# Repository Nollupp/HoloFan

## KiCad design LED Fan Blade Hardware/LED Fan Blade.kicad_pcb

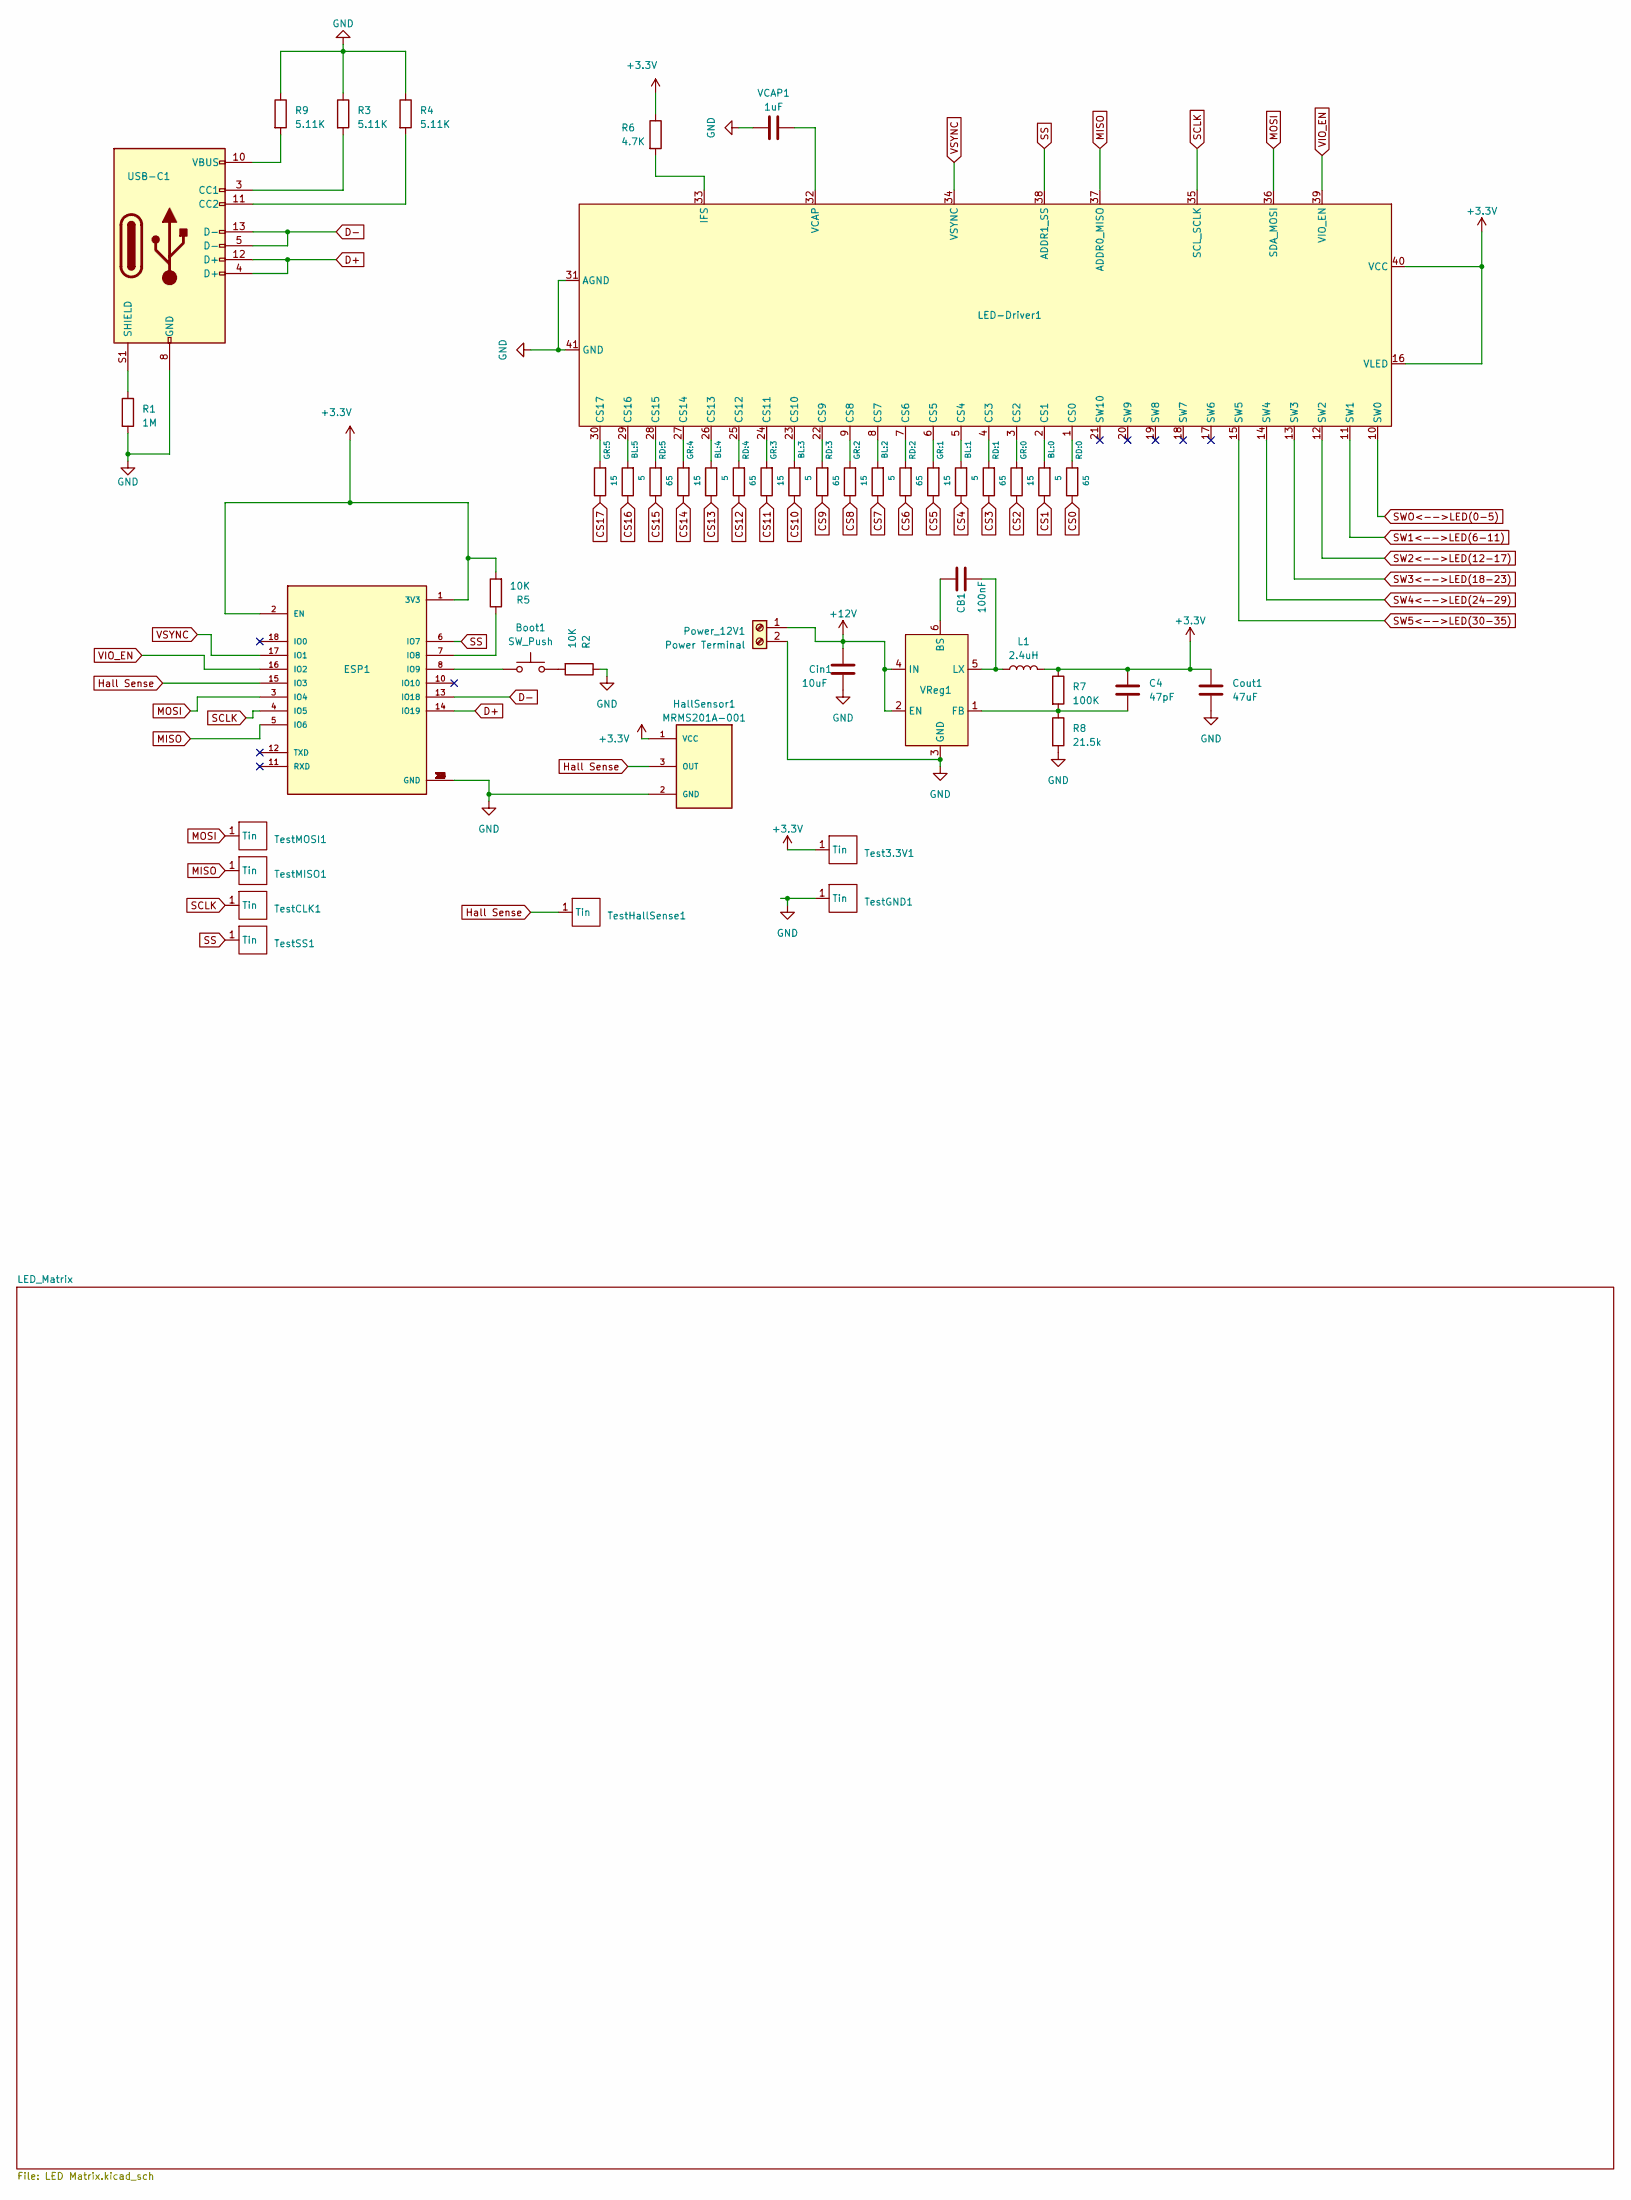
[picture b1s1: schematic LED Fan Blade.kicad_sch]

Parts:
BL:0, BL:1, BL:2, BL:3, BL:4, BL:5: 5; Resistor_603
Boot1: SW_Push; ButtonSMD
C4: 47pF; Cap_603
CB1: 100nF; Cap_603
Cin1: 10uF; Cap_603
Cout1: 47uF; Cap_603
ESP1: ESP32-C3-WROOM-02-N4; MODULE_ESP32-C3-WROOM-02-H4
GR:0, GR:1, GR:2, GR:3, GR:4, GR:5: 15; Resistor_603
HallSensor1: MRMS201A-001; XDCR_MRMS201A-001; PARTREV 9
L1: 2.4uH; Inductor_Sunlord
LED-Driver1: QFN-40_EP_4.85x5.15_Pitch0.4mm
Power_12V1: Power Terminal; Power_Terminal
R1: 1M; Resistor_603
R2, R5: 10K; Resistor_603
R3, R4, R9: 5.11K; Resistor_603
R6: 4.7K; Resistor_603
R7: 100K; Resistor_603
R8: 21.5k; Resistor_603
RD:0, RD:1, RD:2, RD:3, RD:4, RD:5: 65; Resistor_603
Test3.3V1: Test_Point
TestCLK1: Test_Point
TestGND1: Test_Point
TestHallSense1: Test_Point
TestMISO1: Test_Point
TestMOSI1: Test_Point
TestSS1: Test_Point
USB-C1: USB_C_Receptacle_USB2.0; TYPE-C-31-M-15
VCAP1: 1uF; Cap_603
VReg1: AN_SY8105

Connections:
+3.3V: C4.1, Cout1.1, ESP1.1 (3V3), ESP1.2 (EN), HallSensor1.1 (VCC), L1.2, LED-Driver1.16 (VLED), LED-Driver1.40 (VCC), R5.2, R6.1, R7.1, Test3.3V1.1 (Tin)
+12V: Cin1.1, Power_12V1.1, VReg1.2 (EN), VReg1.4 (IN)
CS0: RD:0.1; also elsewhere on the board
CS1: BL:0.1; also elsewhere on the board
CS2: GR:0.1; also elsewhere on the board
CS3: RD:1.1; also elsewhere on the board
CS4: BL:1.1; also elsewhere on the board
CS5: GR:1.1; also elsewhere on the board
CS6: RD:2.1; also elsewhere on the board
CS7: BL:2.1; also elsewhere on the board
CS8: GR:2.1; also elsewhere on the board
CS9: RD:3.1; also elsewhere on the board
CS10: BL:3.1; also elsewhere on the board
CS11: GR:3.1; also elsewhere on the board
CS12: RD:4.1; also elsewhere on the board
CS13: BL:4.1; also elsewhere on the board
CS14: GR:4.1; also elsewhere on the board
CS15: RD:5.1; also elsewhere on the board
CS16: BL:5.1; also elsewhere on the board
CS17: GR:5.1; also elsewhere on the board
D+: ESP1.14 (IO19), USB-C1.4 (D+), USB-C1.12 (D+)
D-: ESP1.13 (IO18), USB-C1.5 (D-), USB-C1.13 (D-)
GND: Cin1.2, Cout1.2, ESP1.9 (GND), ESP1.19 (GND), ESP1.20 (GND), ESP1.21 (GND), ESP1.22 (GND), ESP1.23 (GND), ESP1.24 (GND), ESP1.25 (GND), ESP1.26 (GND), ESP1.27 (GND), ESP1.28 (GND), ESP1.29 (GND), ESP1.30 (GND), ESP1.31 (GND), ESP1.32 (GND), ESP1.33 (GND), ESP1.34 (GND), ESP1.35 (GND), ESP1.36 (GND), ESP1.37 (GND), ESP1.38 (GND), ESP1.39 (GND), HallSensor1.2 (GND), LED-Driver1.31 (AGND), LED-Driver1.41 (GND), Power_12V1.2, R1.2, R2.1, R3.1, R4.1, R8.2, R9.1, TestGND1.1 (Tin), USB-C1.1 (GND), USB-C1.8 (GND), USB-C1.9 (GND), USB-C1.16 (GND), VCAP1.2, VReg1.3 (GND)
Hall Sense: ESP1.15 (IO3), HallSensor1.3 (OUT), TestHallSense1.1 (Tin)
MISO: ESP1.5 (IO6), LED-Driver1.37 (ADDR0_MISO), TestMISO1.1 (Tin)
MOSI: ESP1.3 (IO4), LED-Driver1.36 (SDA_MOSI), TestMOSI1.1 (Tin)
unnamed: Boot1.2, R2.2
unnamed: ESP1.7 (IO8), R5.1
unnamed: Boot1.1, ESP1.8 (IO9)
unnamed: LED-Driver1.1 (CS0), RD:0.2
unnamed: BL:0.2, LED-Driver1.2 (CS1)
unnamed: GR:0.2, LED-Driver1.3 (CS2)
unnamed: LED-Driver1.4 (CS3), RD:1.2
unnamed: BL:1.2, LED-Driver1.5 (CS4)
unnamed: GR:1.2, LED-Driver1.6 (CS5)
unnamed: LED-Driver1.7 (CS6), RD:2.2
unnamed: BL:2.2, LED-Driver1.8 (CS7)
unnamed: GR:2.2, LED-Driver1.9 (CS8)
unnamed: LED-Driver1.22 (CS9), RD:3.2
unnamed: BL:3.2, LED-Driver1.23 (CS10)
unnamed: GR:3.2, LED-Driver1.24 (CS11)
unnamed: LED-Driver1.25 (CS12), RD:4.2
unnamed: BL:4.2, LED-Driver1.26 (CS13)
unnamed: GR:4.2, LED-Driver1.27 (CS14)
unnamed: LED-Driver1.28 (CS15), RD:5.2
unnamed: BL:5.2, LED-Driver1.29 (CS16)
unnamed: GR:5.2, LED-Driver1.30 (CS17)
unnamed: LED-Driver1.33 (IFS), R6.2
unnamed: LED-Driver1.32 (VCAP), VCAP1.1
unnamed: R9.2, USB-C1.2 (VBUS), USB-C1.7 (VBUS), USB-C1.10 (VBUS), USB-C1.15 (VBUS)
unnamed: R3.2, USB-C1.3 (CC1)
unnamed: R4.2, USB-C1.11 (CC2)
unnamed: R1.1, USB-C1.S1 (SHIELD)
unnamed: CB1.1, VReg1.6 (BS)
unnamed: C4.2, R7.2, R8.1, VReg1.1 (FB)
unnamed: CB1.2, L1.1, VReg1.5 (LX)
SCLK: ESP1.4 (IO5), LED-Driver1.35 (SCL_SCLK), TestCLK1.1 (Tin)
SS: ESP1.6 (IO7), LED-Driver1.38 (ADDR1_SS), TestSS1.1 (Tin)
SW1<-->LED(6-11): LED-Driver1.11 (SW1); also elsewhere on the board
SW2<-->LED(12-17): LED-Driver1.12 (SW2); also elsewhere on the board
SW3<-->LED(18-23): LED-Driver1.13 (SW3); also elsewhere on the board
SW4<-->LED(24-29): LED-Driver1.14 (SW4); also elsewhere on the board
SW5<-->LED(30-35): LED-Driver1.15 (SW5); also elsewhere on the board
SWO<-->LED(0-5): LED-Driver1.10 (SW0); also elsewhere on the board
VIO_EN: ESP1.16 (IO2), LED-Driver1.39 (VIO_EN)
VSYNC: ESP1.17 (IO1), LED-Driver1.34 (VSYNC)

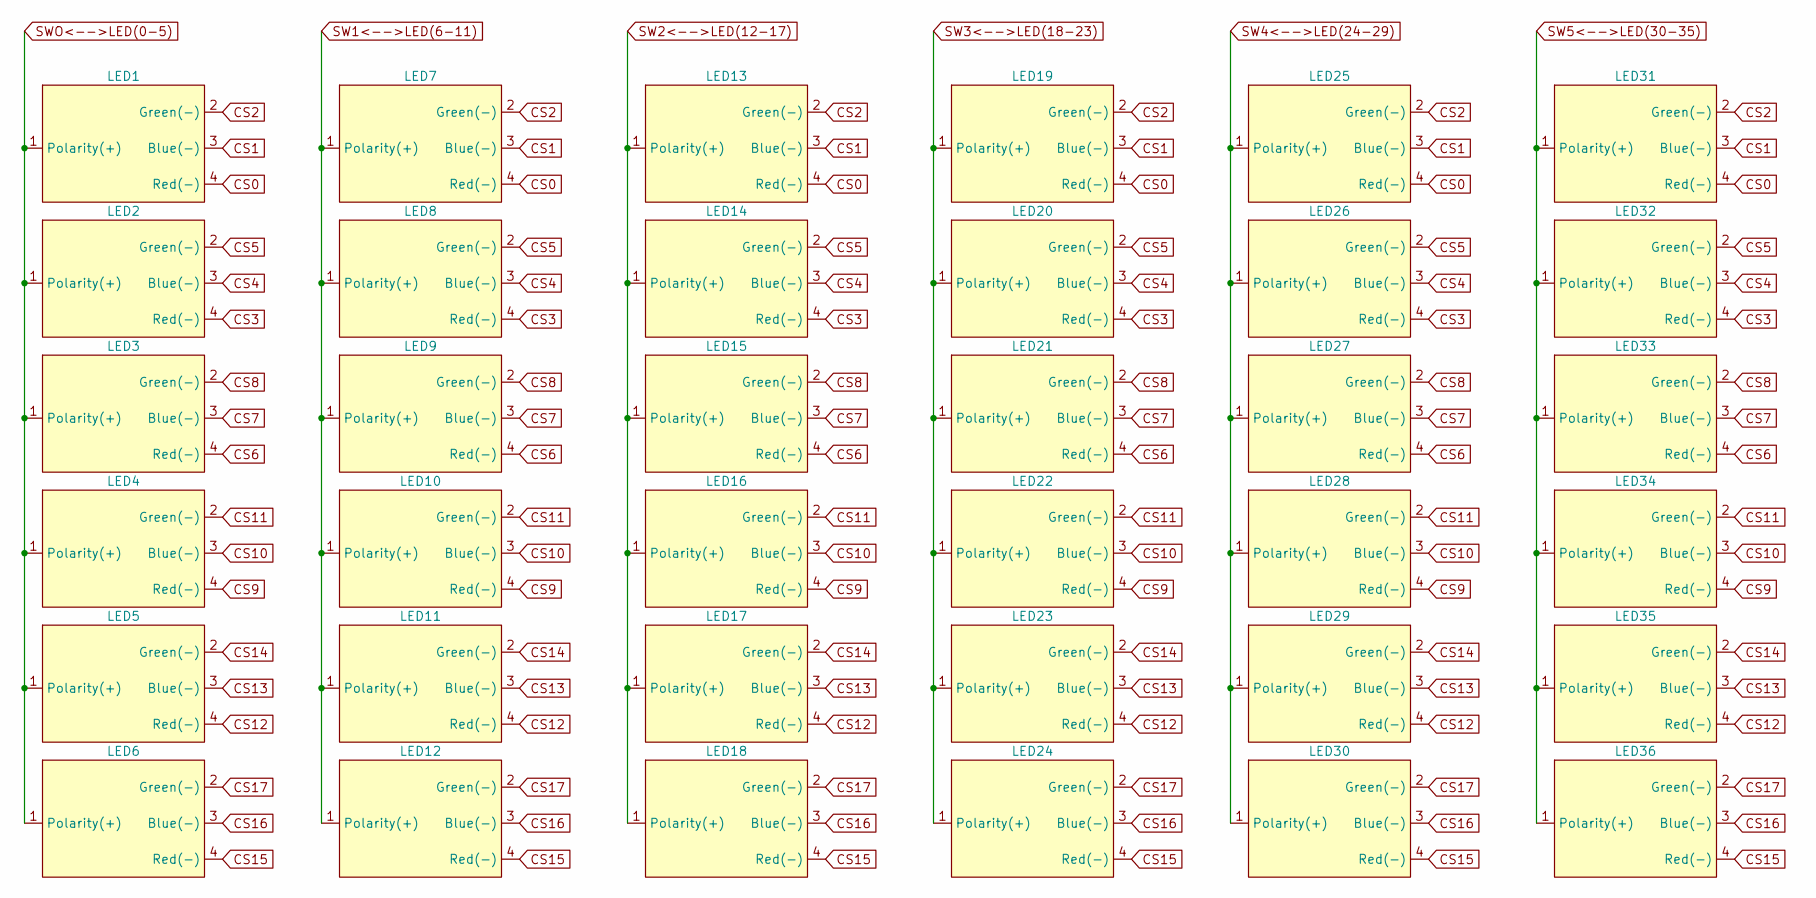
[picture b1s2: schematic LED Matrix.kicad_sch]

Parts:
LED1, LED2, LED3, LED4, LED5, LED6, LED7, LED8, LED9, LED10, LED11, LED12, LED13, LED14, LED15, LED16, LED17, LED18, LED19, LED20, LED21, LED22, LED23, LED24, LED25, LED26, LED27, LED28, LED29, LED30, LED31, LED32, LED33, LED34, LED35, LED36: WL-SFCW SMT Full-color Chip LED

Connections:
CS0: LED1.4 (Red(-)), LED7.4 (Red(-)), LED13.4 (Red(-)), LED19.4 (Red(-)), LED25.4 (Red(-)), LED31.4 (Red(-)); also elsewhere on the board
CS1: LED1.3 (Blue(-)), LED7.3 (Blue(-)), LED13.3 (Blue(-)), LED19.3 (Blue(-)), LED25.3 (Blue(-)), LED31.3 (Blue(-)); also elsewhere on the board
CS2: LED1.2 (Green(-)), LED7.2 (Green(-)), LED13.2 (Green(-)), LED19.2 (Green(-)), LED25.2 (Green(-)), LED31.2 (Green(-)); also elsewhere on the board
CS3: LED2.4 (Red(-)), LED8.4 (Red(-)), LED14.4 (Red(-)), LED20.4 (Red(-)), LED26.4 (Red(-)), LED32.4 (Red(-)); also elsewhere on the board
CS4: LED2.3 (Blue(-)), LED8.3 (Blue(-)), LED14.3 (Blue(-)), LED20.3 (Blue(-)), LED26.3 (Blue(-)), LED32.3 (Blue(-)); also elsewhere on the board
CS5: LED2.2 (Green(-)), LED8.2 (Green(-)), LED14.2 (Green(-)), LED20.2 (Green(-)), LED26.2 (Green(-)), LED32.2 (Green(-)); also elsewhere on the board
CS6: LED3.4 (Red(-)), LED9.4 (Red(-)), LED15.4 (Red(-)), LED21.4 (Red(-)), LED27.4 (Red(-)), LED33.4 (Red(-)); also elsewhere on the board
CS7: LED3.3 (Blue(-)), LED9.3 (Blue(-)), LED15.3 (Blue(-)), LED21.3 (Blue(-)), LED27.3 (Blue(-)), LED33.3 (Blue(-)); also elsewhere on the board
CS8: LED3.2 (Green(-)), LED9.2 (Green(-)), LED15.2 (Green(-)), LED21.2 (Green(-)), LED27.2 (Green(-)), LED33.2 (Green(-)); also elsewhere on the board
CS9: LED4.4 (Red(-)), LED10.4 (Red(-)), LED16.4 (Red(-)), LED22.4 (Red(-)), LED28.4 (Red(-)), LED34.4 (Red(-)); also elsewhere on the board
CS10: LED4.3 (Blue(-)), LED10.3 (Blue(-)), LED16.3 (Blue(-)), LED22.3 (Blue(-)), LED28.3 (Blue(-)), LED34.3 (Blue(-)); also elsewhere on the board
CS11: LED4.2 (Green(-)), LED10.2 (Green(-)), LED16.2 (Green(-)), LED22.2 (Green(-)), LED28.2 (Green(-)), LED34.2 (Green(-)); also elsewhere on the board
CS12: LED5.4 (Red(-)), LED11.4 (Red(-)), LED17.4 (Red(-)), LED23.4 (Red(-)), LED29.4 (Red(-)), LED35.4 (Red(-)); also elsewhere on the board
CS13: LED5.3 (Blue(-)), LED11.3 (Blue(-)), LED17.3 (Blue(-)), LED23.3 (Blue(-)), LED29.3 (Blue(-)), LED35.3 (Blue(-)); also elsewhere on the board
CS14: LED5.2 (Green(-)), LED11.2 (Green(-)), LED17.2 (Green(-)), LED23.2 (Green(-)), LED29.2 (Green(-)), LED35.2 (Green(-)); also elsewhere on the board
CS15: LED6.4 (Red(-)), LED12.4 (Red(-)), LED18.4 (Red(-)), LED24.4 (Red(-)), LED30.4 (Red(-)), LED36.4 (Red(-)); also elsewhere on the board
CS16: LED6.3 (Blue(-)), LED12.3 (Blue(-)), LED18.3 (Blue(-)), LED24.3 (Blue(-)), LED30.3 (Blue(-)), LED36.3 (Blue(-)); also elsewhere on the board
CS17: LED6.2 (Green(-)), LED12.2 (Green(-)), LED18.2 (Green(-)), LED24.2 (Green(-)), LED30.2 (Green(-)), LED36.2 (Green(-)); also elsewhere on the board
SW1<-->LED(6-11): LED7.1 (Polarity(+)), LED8.1 (Polarity(+)), LED9.1 (Polarity(+)), LED10.1 (Polarity(+)), LED11.1 (Polarity(+)), LED12.1 (Polarity(+)); also elsewhere on the board
SW2<-->LED(12-17): LED13.1 (Polarity(+)), LED14.1 (Polarity(+)), LED15.1 (Polarity(+)), LED16.1 (Polarity(+)), LED17.1 (Polarity(+)), LED18.1 (Polarity(+)); also elsewhere on the board
SW3<-->LED(18-23): LED19.1 (Polarity(+)), LED20.1 (Polarity(+)), LED21.1 (Polarity(+)), LED22.1 (Polarity(+)), LED23.1 (Polarity(+)), LED24.1 (Polarity(+)); also elsewhere on the board
SW4<-->LED(24-29): LED25.1 (Polarity(+)), LED26.1 (Polarity(+)), LED27.1 (Polarity(+)), LED28.1 (Polarity(+)), LED29.1 (Polarity(+)), LED30.1 (Polarity(+)); also elsewhere on the board
SW5<-->LED(30-35): LED31.1 (Polarity(+)), LED32.1 (Polarity(+)), LED33.1 (Polarity(+)), LED34.1 (Polarity(+)), LED35.1 (Polarity(+)), LED36.1 (Polarity(+)); also elsewhere on the board
SWO<-->LED(0-5): LED1.1 (Polarity(+)), LED2.1 (Polarity(+)), LED3.1 (Polarity(+)), LED4.1 (Polarity(+)), LED5.1 (Polarity(+)), LED6.1 (Polarity(+)); also elsewhere on the board

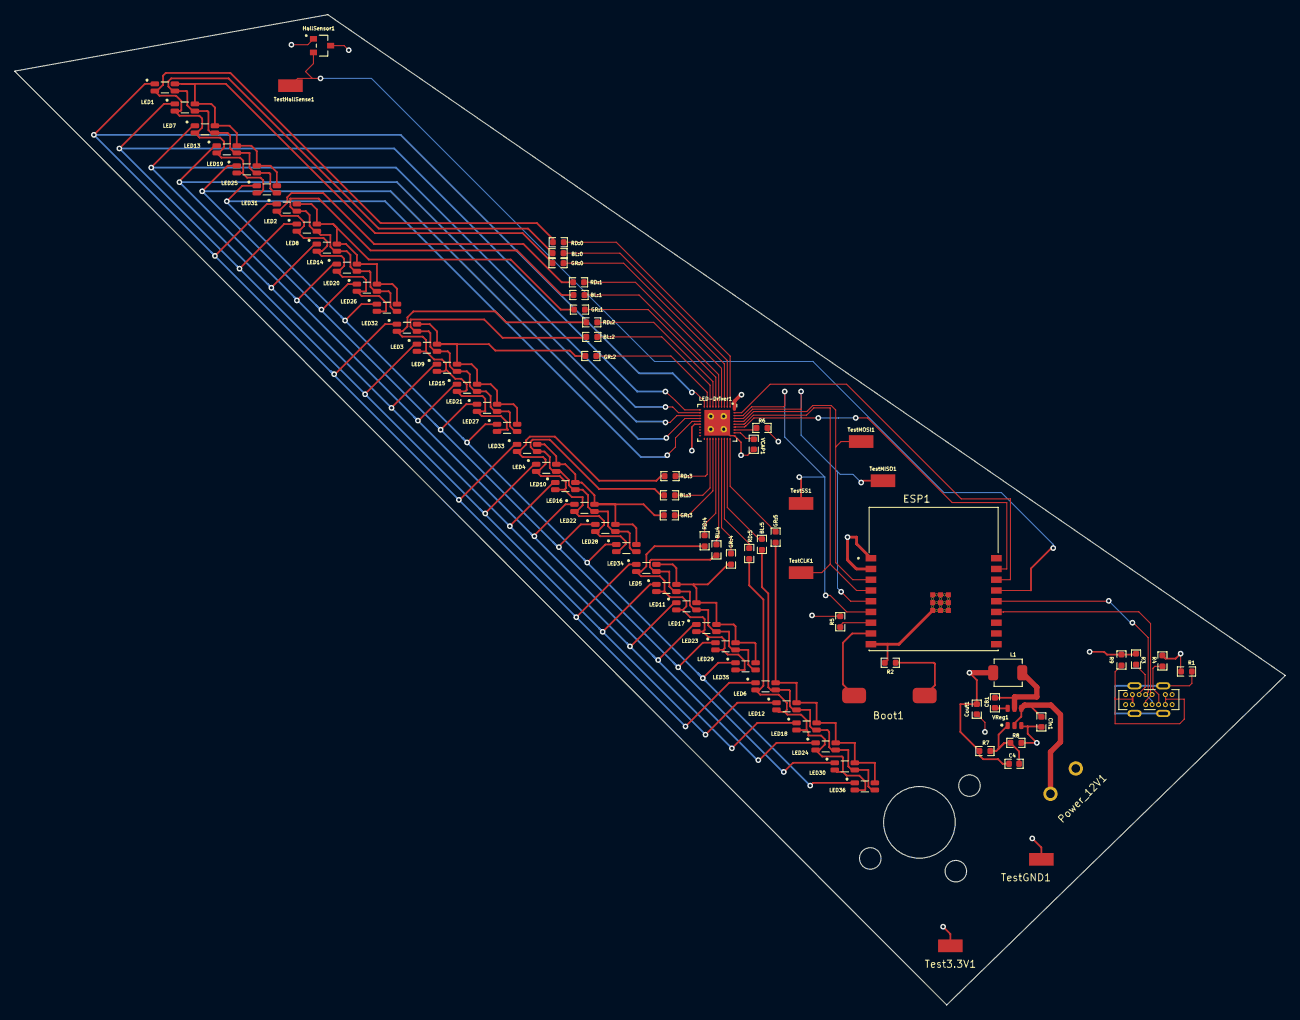
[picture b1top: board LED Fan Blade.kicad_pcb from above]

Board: 4 copper layers, 177.3 x 138.2 mm, 83 parts (0 on the bottom side), 66 nets.

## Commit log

2023-03-04 First commit, PCB files and sample code
2023-03-09 Finished up PCB
2023-03-10 Changed PCB
2023-03-11 Changed USB C connector to different one
2023-04-03 Moved stuff, got repo for code ready
